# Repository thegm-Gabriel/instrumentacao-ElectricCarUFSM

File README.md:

<div align="center">
  
  <h1>Carro Elétrico UFSM-CS</h1>
  <p><strong>Um laboratório em movimento.</strong></p>
  <p><strong>NEXUS</strong> · sistema de instrumentação, telemetria e controle experimental do veículo</p>
  <p>Universidade Federal de Santa Maria · Campus Cachoeira do Sul</p>
  <p>
    <a href="#o-projeto">O projeto</a> ·
    <a href="#o-sistema">O sistema</a> ·
    <a href="#por-onde-começar">Por onde começar</a> ·
    <a href="documentacao/README.md">Documentação completa</a>
  </p>
</div>

---

## O projeto

O carro reúne, em um veículo experimental, conhecimentos de circuitos,
acionamentos, programação, energia, medição e mecânica. Construí-lo e testá-lo
permite que estudantes confrontem hipóteses com dados reais e entendam como as
decisões de uma área afetam as demais.

O **NEXUS** reúne a instrumentação, a telemetria e o controle experimental do
carro. O nome vem do latim *nexus* (“ligação” ou “vínculo”) e expressa seu
papel de integrar sensores, módulos e informações em uma visão acessível do
veículo. A equipe observa leituras e falhas durante os testes; visitantes
podem conhecer o movimento do carro por um painel de leitura simples. O
projeto também busca aproximar a universidade da comunidade e despertar
interesse pela engenharia e pela mobilidade elétrica.

## O sistema

No NEXUS, três ESP32-S3 dividem aquisição, operação e apresentação dos dados:

```mermaid
flowchart LR
    S["Sensores e encoders"] --> M["ESP32-S3 Mestre"]
    M <-->|UART| E["ESP32-S3 Equipe"]
    M <-->|UART| V["ESP32-S3 Visitantes"]
    M <-->|SPI2| SD["microSD · histórico e logs"]
    E <-->|Wi-Fi / HTTP| PE["Navegador · painel técnico"]
    V <-->|Wi-Fi / HTTP| PV["Navegador · painel público"]
```

| Componente | O que faz |
|---|---|
| **Mestre** | Lê sensores e encoders, calcula a telemetria, registra dados e diagnóstico no microSD e coordena comandos e atualizações OTA. |
| **Equipe** | Recebe a telemetria por UART, hospeda o painel técnico e encaminha consultas e ações ao mestre. |
| **Visitantes** | Recebe a telemetria por UART e apresenta uma página pública de leitura. |
| **Código compartilhado** | Define os formatos dos dados, o enlace UART e os serviços comuns aos firmwares. |

Os firmwares são projetos independentes **PlatformIO/ESP-IDF** em
[`firmware/`](firmware/). A equipe dispõe de páginas separadas para telemetria,
comandos, controle preparatório e diagnóstico dos ESPs. O painel público mostra
as leituras do veículo sem controles de operação.

> **Estado atual do controle:** pedidos de marcha, limites e parada remota são
> registrados no mestre, mas **não acionam fisicamente o veículo**. Ações pelo
> painel da equipe ficam disponíveis aos clientes do AP da Equipe. Veja
> [controle remoto](documentacao/controle-remoto.md) e
> [acesso aos satélites](documentacao/satelites.md).

## Por onde começar

- **Conhecer o funcionamento:** [visão geral da documentação](documentacao/README.md),
  [arquitetura](documentacao/arquitetura.md) e
  [filosofia do código](documentacao/filosofia.md). Para siglas e recursos do
  ESP32-S3, consulte o [glossário e guia de periféricos](documentacao/conceitos.md).
- **Montar e testar:** [pinagem e níveis elétricos](documentacao/pinagem.md),
  [guia do mestre](documentacao/mestre.md) e
  [guia dos satélites](documentacao/satelites.md).
- **Desenvolver e publicar:** [ferramentas](documentacao/ferramentas.md),
  [versionamento, releases e atualização OTA](documentacao/ota.md).

## Equipe

**Orientação:** Prof. Dr. Paulo César Vargas Luz.

**Equipe discente desta etapa de instrumentação:**

- Adylson Hahn
- Érick Ramon Biscaglia
- Gabriel Muttoni
- Gustavo Reckziegel Machado
- Théos Schultz Tompsen

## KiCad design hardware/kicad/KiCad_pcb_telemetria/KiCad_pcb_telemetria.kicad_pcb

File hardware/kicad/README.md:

# Projetos KiCad

Pasta reservada para esquemas elétricos, placas e bibliotecas locais do KiCad.

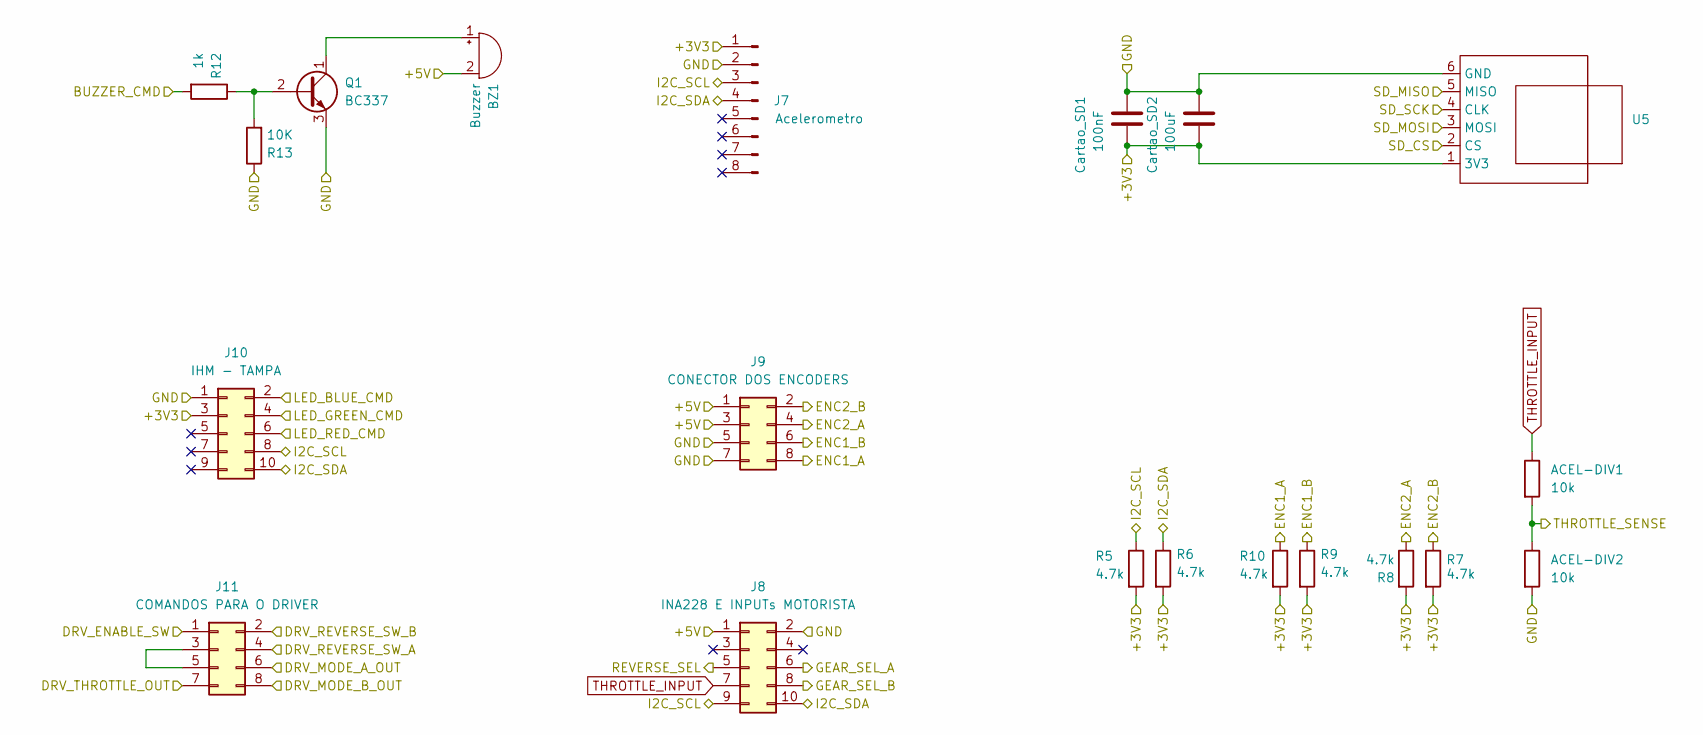
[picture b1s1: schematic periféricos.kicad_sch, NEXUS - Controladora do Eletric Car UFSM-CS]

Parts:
ACEL-DIV1, ACEL-DIV2: 10k; R_Axial_DIN0204_L3.6mm_D1.6mm_P5.08mm_Horizontal
BZ1: Buzzer; Buzzer_D14mm_H7mm_P10mm
Cartao_SD1: 100nF; C_Radial_D5.0mm_H11.0mm_P2.00mm
Cartao_SD2: 100uF; C_Radial_D5.0mm_H11.0mm_P2.00mm
J7: Acelerometro; PinHeader_1x08_P2.54mm_Vertical
J8: INA228 E INPUTs MOTORISTA; JST_PUD_B10B-PUDSS_2x05_P2.00mm_Vertical
J9: CONECTOR DOS ENCODERS; JST_PUD_B08B-PUDSS_2x04_P2.00mm_Vertical
J10: IHM - TAMPA; JST_PUD_B10B-PUDSS_2x05_P2.00mm_Vertical
J11: COMANDOS PARA O DRIVER; JST_PUD_B08B-PUDSS_2x04_P2.00mm_Vertical
Q1: BC337; TO-92
R5, R6, R7, R8, R9, R10: 4.7k; R_Axial_DIN0204_L3.6mm_D1.6mm_P5.08mm_Horizontal
R12: 1k; R_Axial_DIN0204_L3.6mm_D1.6mm_P5.08mm_Horizontal
R13: 10K; R_Axial_DIN0204_L3.6mm_D1.6mm_P5.08mm_Horizontal
U5: CartãoSD-MODULO

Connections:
+3V3: Cartao_SD1.2, Cartao_SD2.2, J7.1, J10.3, R5.2, R6.2, R7.2, R8.2, R9.2, R10.2, U5.1 (3V3); also elsewhere on the board
+5V: BZ1.2 (-), J8.1, J9.1, J9.3; also elsewhere on the board
/CONTROLE DO DRIVER/DRV_ENABLE_SW: J11.1; also elsewhere on the board
/CONTROLE DO DRIVER/DRV_MODE_A_OUT: J11.6; also elsewhere on the board
/CONTROLE DO DRIVER/DRV_MODE_B_OUT: J11.8; also elsewhere on the board
/CONTROLE DO DRIVER/DRV_REVERSE_SW_A: J11.4; also elsewhere on the board
/CONTROLE DO DRIVER/DRV_REVERSE_SW_B: J11.2; also elsewhere on the board
/CONTROLE DO DRIVER/DRV_THROTTLE_OUT: J11.7; also elsewhere on the board
/ESP32-S3-MESTRE/BUZZER_CMD: R12.2; also elsewhere on the board
/ESP32-S3-MESTRE/ENC1_A: J9.8, R10.1; also elsewhere on the board
/ESP32-S3-MESTRE/ENC1_B: J9.6, R9.1; also elsewhere on the board
/ESP32-S3-MESTRE/ENC2_A: J9.4, R8.1; also elsewhere on the board
/ESP32-S3-MESTRE/ENC2_B: J9.2, R7.1; also elsewhere on the board
/ESP32-S3-MESTRE/GEAR_SEL_A: J8.6; also elsewhere on the board
/ESP32-S3-MESTRE/GEAR_SEL_B: J8.8; also elsewhere on the board
/ESP32-S3-MESTRE/LED_BLUE_CMD: J10.2; also elsewhere on the board
/ESP32-S3-MESTRE/LED_GREEN_CMD: J10.4; also elsewhere on the board
/ESP32-S3-MESTRE/LED_RED_CMD: J10.6; also elsewhere on the board
/ESP32-S3-MESTRE/REVERSE_SEL: J8.5; also elsewhere on the board
/ESP32-S3-MESTRE/SD_CS: U5.2 (CS); also elsewhere on the board
/ESP32-S3-MESTRE/SD_MISO: U5.5 (MISO); also elsewhere on the board
/ESP32-S3-MESTRE/SD_MOSI: U5.3 (MOSI); also elsewhere on the board
/ESP32-S3-MESTRE/SD_SCK: U5.4 (CLK); also elsewhere on the board
/ESP32-S3-MESTRE/THROTTLE_SENSE: ACEL-DIV1.2, ACEL-DIV2.1; also elsewhere on the board
GND: ACEL-DIV2.2, Cartao_SD1.1, Cartao_SD2.1, J7.2, J8.2, J9.5, J9.7, J10.1, Q1.3 (E), R13.1, U5.6 (GND); also elsewhere on the board
I2C_SCL: J7.3, J8.9, J10.8, R5.1; also elsewhere on the board
I2C_SDA: J7.4, J8.10, J10.10, R6.1; also elsewhere on the board
unnamed: BZ1.1 (+), Q1.1 (C)
unnamed: J11.3, J11.5
unnamed: Q1.2 (B), R12.1, R13.2
THROTTLE_INPUT: ACEL-DIV1.1, J8.7

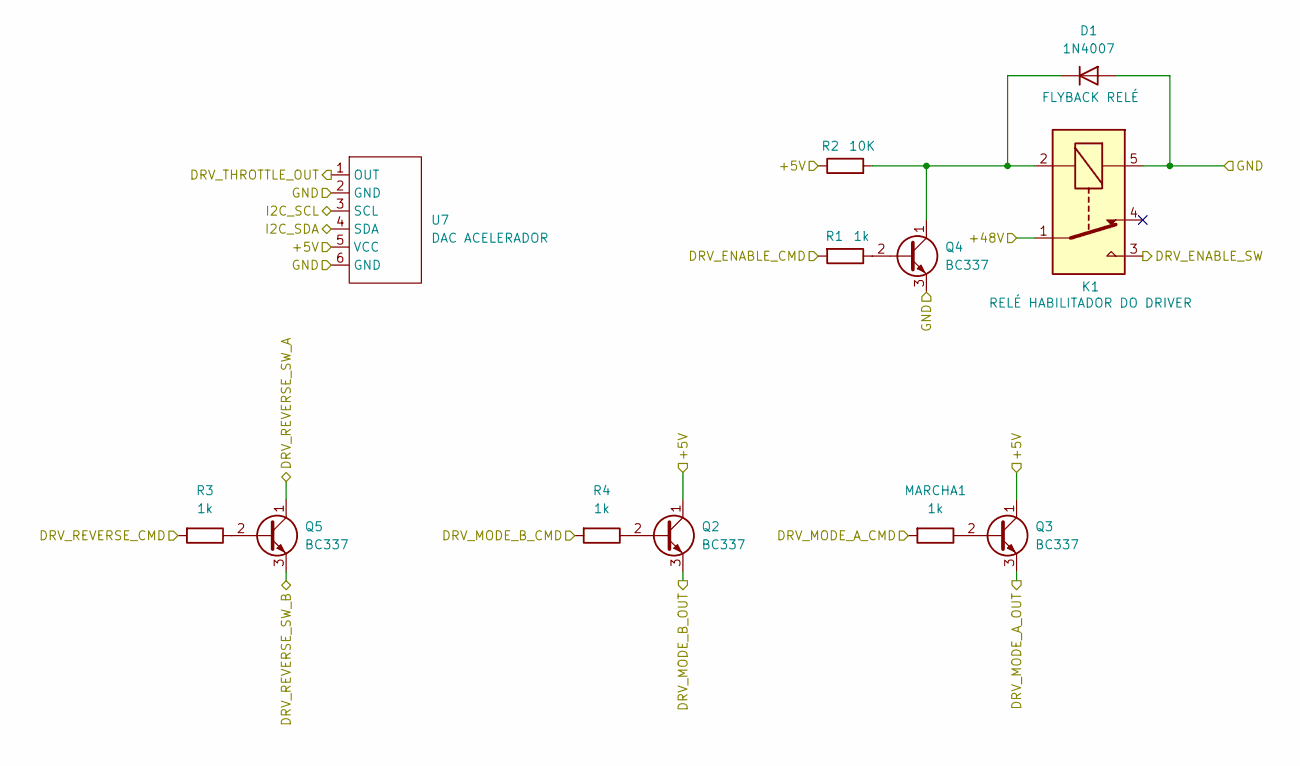
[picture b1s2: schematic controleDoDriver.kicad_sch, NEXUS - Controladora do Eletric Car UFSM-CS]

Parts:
D1: 1N4007; D_DO-41_SOD81_P10.16mm_Horizontal
K1: SANYOU_SRD_Form_C; Relay_SPDT_SANYOU_SRD_Series_Form_C
MARCHA1: 1k; R_Axial_DIN0204_L3.6mm_D1.6mm_P5.08mm_Horizontal
Q2, Q3, Q4, Q5: BC337; TO-92
R1, R3, R4: 1k; R_Axial_DIN0204_L3.6mm_D1.6mm_P5.08mm_Horizontal
R2: 10K; R_Axial_DIN0204_L3.6mm_D1.6mm_P5.08mm_Horizontal
U7: MCP4725

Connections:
+5V: Q2.1 (C), Q3.1 (C), R2.1, U7.5 (VCC); also elsewhere on the board
+48V: K1.1; also elsewhere on the board
/CONTROLE DO DRIVER/DRV_ENABLE_CMD: R1.2; also elsewhere on the board
/CONTROLE DO DRIVER/DRV_ENABLE_SW: K1.3; also elsewhere on the board
/CONTROLE DO DRIVER/DRV_MODE_A_CMD: MARCHA1.2; also elsewhere on the board
/CONTROLE DO DRIVER/DRV_MODE_A_OUT: Q3.3 (E); also elsewhere on the board
/CONTROLE DO DRIVER/DRV_MODE_B_CMD: R4.2; also elsewhere on the board
/CONTROLE DO DRIVER/DRV_MODE_B_OUT: Q2.3 (E); also elsewhere on the board
/CONTROLE DO DRIVER/DRV_REVERSE_CMD: R3.2; also elsewhere on the board
/CONTROLE DO DRIVER/DRV_REVERSE_SW_A: Q5.1 (C); also elsewhere on the board
/CONTROLE DO DRIVER/DRV_REVERSE_SW_B: Q5.3 (E); also elsewhere on the board
/CONTROLE DO DRIVER/DRV_THROTTLE_OUT: U7.1 (OUT); also elsewhere on the board
GND: D1.2 (A), K1.5, Q4.3 (E), U7.2 (GND), U7.6 (GND); also elsewhere on the board
I2C_SCL: U7.3 (SCL); also elsewhere on the board
I2C_SDA: U7.4 (SDA); also elsewhere on the board
unnamed: D1.1 (K), K1.2, Q4.1 (C), R2.2
unnamed: Q2.2 (B), R4.1
unnamed: MARCHA1.1, Q3.2 (B)
unnamed: Q4.2 (B), R1.1
unnamed: Q5.2 (B), R3.1

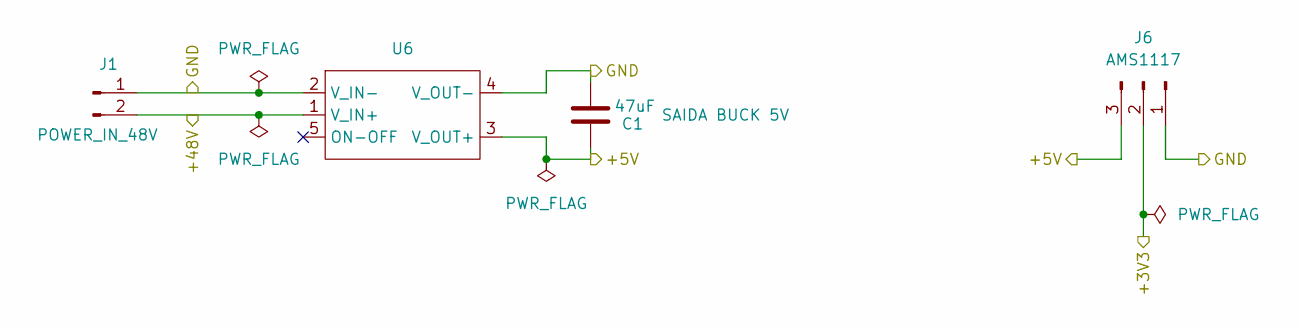
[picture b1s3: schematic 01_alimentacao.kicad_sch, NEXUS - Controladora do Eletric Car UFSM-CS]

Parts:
C1: 47uF; C_Radial_D5.0mm_H11.0mm_P2.00mm
J1: POWER_IN_48V; SolderWire-0.75sqmm_1x02_P4.8mm_D1.25mm_OD2.3mm
J6: AMS1117; PinHeader_1x03_P2.54mm_Vertical
U6: ConversorBUCK_100V_5V-2A

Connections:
+3V3: J6.2; also elsewhere on the board
+5V: C1.1, J6.3, U6.3 (V_OUT+); also elsewhere on the board
+48V: J1.2, U6.1 (V_IN+); also elsewhere on the board
GND: C1.2, J1.1, J6.1, U6.2 (V_IN-), U6.4 (V_OUT-); also elsewhere on the board

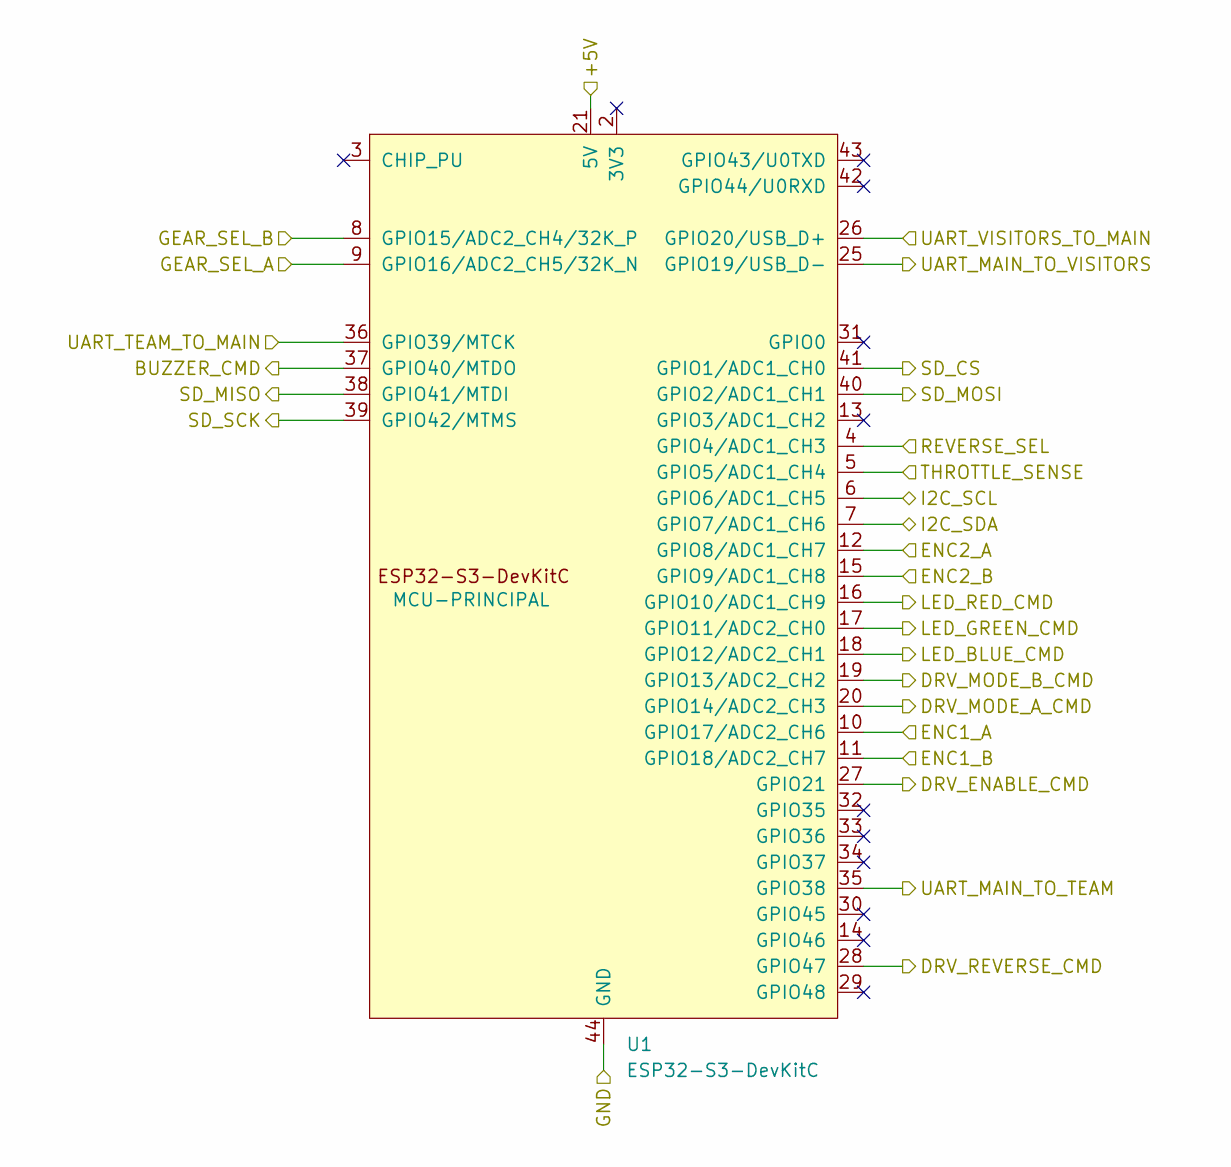
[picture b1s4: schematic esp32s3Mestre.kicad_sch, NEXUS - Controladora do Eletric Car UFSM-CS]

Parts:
U1: ESP32-S3-DevKitC

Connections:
+5V: U1.21 (5V); also elsewhere on the board
/COMUNICAÇÃO WI-FI/UART_MAIN_TO_TEAM: U1.36 (GPIO39/MTCK); also elsewhere on the board
/COMUNICAÇÃO WI-FI/UART_MAIN_TO_VISITORS: U1.25 (GPIO19/USB_D-); also elsewhere on the board
/COMUNICAÇÃO WI-FI/UART_TEAM_TO_MAIN: U1.35 (GPIO38); also elsewhere on the board
/COMUNICAÇÃO WI-FI/UART_VISITORS_TO_MAIN: U1.26 (GPIO20/USB_D+); also elsewhere on the board
/CONTROLE DO DRIVER/DRV_ENABLE_CMD: U1.27 (GPIO21); also elsewhere on the board
/CONTROLE DO DRIVER/DRV_MODE_A_CMD: U1.20 (GPIO14/ADC2_CH3); also elsewhere on the board
/CONTROLE DO DRIVER/DRV_MODE_B_CMD: U1.19 (GPIO13/ADC2_CH2); also elsewhere on the board
/CONTROLE DO DRIVER/DRV_REVERSE_CMD: U1.28 (GPIO47); also elsewhere on the board
/ESP32-S3-MESTRE/BUZZER_CMD: U1.37 (GPIO40/MTDO); also elsewhere on the board
/ESP32-S3-MESTRE/ENC1_A: U1.10 (GPIO17/ADC2_CH6); also elsewhere on the board
/ESP32-S3-MESTRE/ENC1_B: U1.11 (GPIO18/ADC2_CH7); also elsewhere on the board
/ESP32-S3-MESTRE/ENC2_A: U1.12 (GPIO8/ADC1_CH7); also elsewhere on the board
/ESP32-S3-MESTRE/ENC2_B: U1.15 (GPIO9/ADC1_CH8); also elsewhere on the board
/ESP32-S3-MESTRE/GEAR_SEL_A: U1.9 (GPIO16/ADC2_CH5/32K_N); also elsewhere on the board
/ESP32-S3-MESTRE/GEAR_SEL_B: U1.8 (GPIO15/ADC2_CH4/32K_P); also elsewhere on the board
/ESP32-S3-MESTRE/LED_BLUE_CMD: U1.18 (GPIO12/ADC2_CH1); also elsewhere on the board
/ESP32-S3-MESTRE/LED_GREEN_CMD: U1.17 (GPIO11/ADC2_CH0); also elsewhere on the board
/ESP32-S3-MESTRE/LED_RED_CMD: U1.16 (GPIO10/ADC1_CH9); also elsewhere on the board
/ESP32-S3-MESTRE/REVERSE_SEL: U1.4 (GPIO4/ADC1_CH3); also elsewhere on the board
/ESP32-S3-MESTRE/SD_CS: U1.41 (GPIO1/ADC1_CH0); also elsewhere on the board
/ESP32-S3-MESTRE/SD_MISO: U1.38 (GPIO41/MTDI); also elsewhere on the board
/ESP32-S3-MESTRE/SD_MOSI: U1.40 (GPIO2/ADC1_CH1); also elsewhere on the board
/ESP32-S3-MESTRE/SD_SCK: U1.39 (GPIO42/MTMS); also elsewhere on the board
/ESP32-S3-MESTRE/THROTTLE_SENSE: U1.5 (GPIO5/ADC1_CH4); also elsewhere on the board
GND: U1.22 (GND), U1.23 (GND), U1.24 (GND), U1.44 (GND); also elsewhere on the board
I2C_SCL: U1.6 (GPIO6/ADC1_CH5); also elsewhere on the board
I2C_SDA: U1.7 (GPIO7/ADC1_CH6); also elsewhere on the board

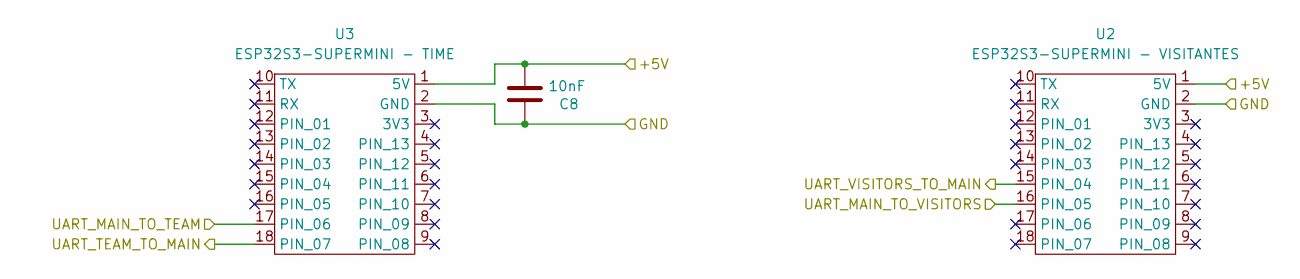
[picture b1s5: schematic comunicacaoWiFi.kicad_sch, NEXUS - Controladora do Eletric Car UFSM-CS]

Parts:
C8: 10nF; C_Radial_D5.0mm_H11.0mm_P2.00mm
U2: ESP32S3-SUPERMINI - VISITANTES; ESP32-S3-SuperMini
U3: ESP32S3-SUPERMINI - TIME; ESP32-S3-SuperMini

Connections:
+5V: C8.2, U2.1 (5V), U3.1 (5V); also elsewhere on the board
/COMUNICAÇÃO WI-FI/UART_MAIN_TO_TEAM: U3.17 (PIN_06); also elsewhere on the board
/COMUNICAÇÃO WI-FI/UART_MAIN_TO_VISITORS: U2.16 (PIN_05); also elsewhere on the board
/COMUNICAÇÃO WI-FI/UART_TEAM_TO_MAIN: U3.18 (PIN_07); also elsewhere on the board
/COMUNICAÇÃO WI-FI/UART_VISITORS_TO_MAIN: U2.15 (PIN_04); also elsewhere on the board
GND: C8.1, U2.2 (GND), U3.2 (GND); also elsewhere on the board

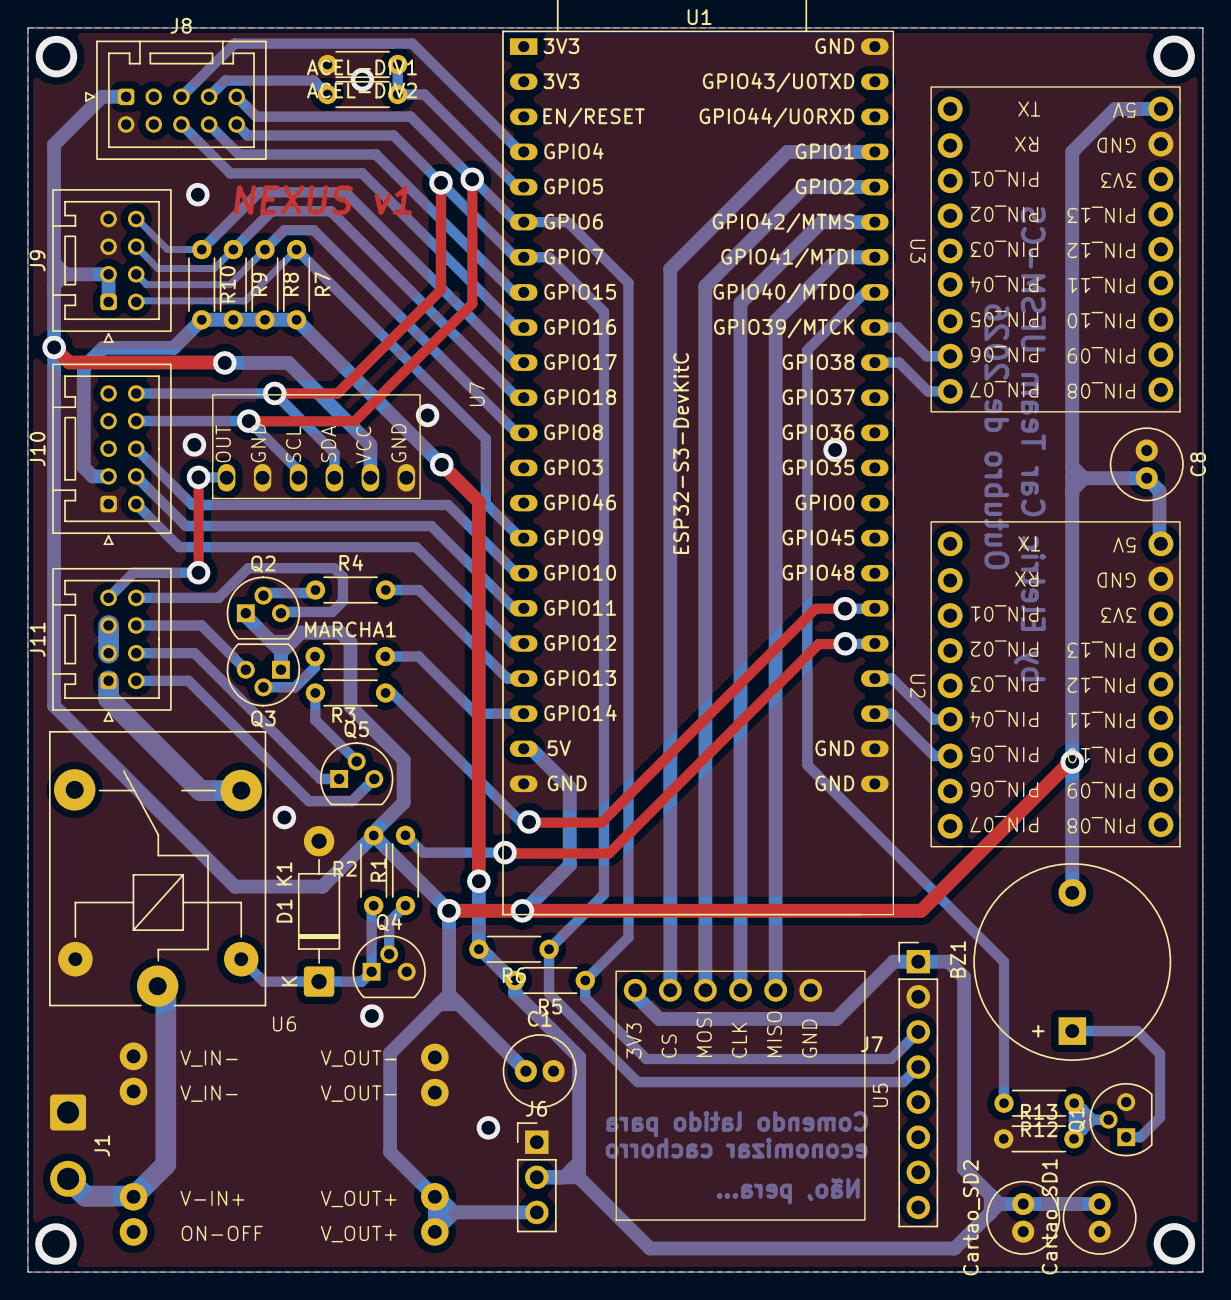
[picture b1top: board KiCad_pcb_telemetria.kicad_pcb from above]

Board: 2 copper layers, 85.0 x 90.0 mm, 40 parts (0 on the bottom side), 45 nets.

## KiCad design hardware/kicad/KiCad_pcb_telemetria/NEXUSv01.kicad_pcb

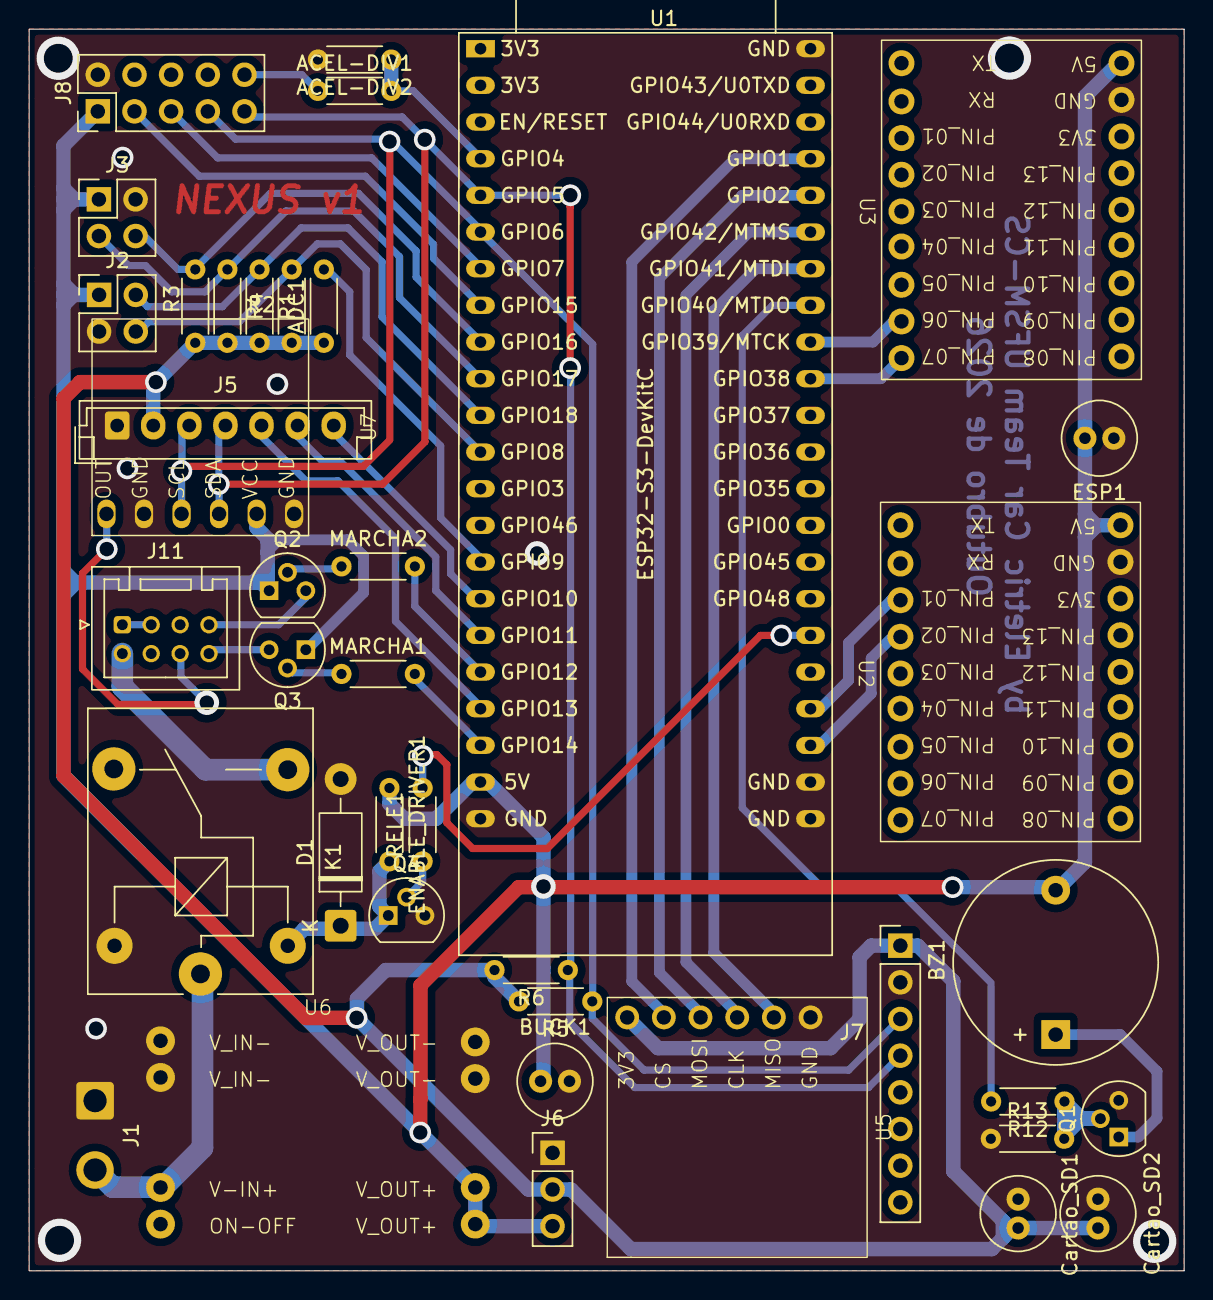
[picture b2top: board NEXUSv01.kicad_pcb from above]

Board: 2 copper layers, 80.0 x 86.0 mm, 40 parts (0 on the bottom side), 41 nets.

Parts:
ACEL-DIV1, ACEL-DIV2: 10k; R_Axial_DIN0204_L3.6mm_D1.6mm_P5.08mm_Horizontal
ADC1: 10k; R_Axial_DIN0204_L3.6mm_D1.6mm_P5.08mm_Horizontal
BUCK1: 47uF; C_Radial_D5.0mm_H11.0mm_P2.00mm
BZ1: Buzzer; Buzzer_D14mm_H7mm_P10mm
Cartao_SD1: 100nF; C_Radial_D5.0mm_H11.0mm_P2.00mm
Cartao_SD2: 100uF; C_Radial_D5.0mm_H11.0mm_P2.00mm
D1: 1N4007; D_DO-41_SOD81_P10.16mm_Horizontal
ENABLE_DRIVER1: 10K; R_Axial_DIN0204_L3.6mm_D1.6mm_P5.08mm_Horizontal
ESP1: 10nF; C_Radial_D5.0mm_H11.0mm_P2.00mm
J1: ALIMENTACAO_48V; SolderWire-0.75sqmm_1x02_P4.8mm_D1.25mm_OD2.3mm
J2, J3: Conn_02x02_Odd_Even; PinHeader_2x02_P2.54mm_Vertical
J5: INDICADOR; JST_EH_B7B-EH-A_1x07_P2.50mm_Vertical
J6: AMS1117; PinHeader_1x03_P2.54mm_Vertical
J7: Acelerometro; PinHeader_1x08_P2.54mm_Vertical
J8: Conn_02x05_Odd_Even; PinHeader_2x05_P2.54mm_Vertical
J11: Conn_02x04_Odd_Even; JST_PUD_B08B-PUDSS_2x04_P2.00mm_Vertical
K1: SANYOU_SRD_Form_C; Relay_SPDT_SANYOU_SRD_Series_Form_C
MARCHA1, MARCHA2: 1k; R_Axial_DIN0204_L3.6mm_D1.6mm_P5.08mm_Horizontal
Q1, Q2, Q3, Q4: BC337; TO-92
R1, R2, R3, R4, R5, R6: 4.7k; R_Axial_DIN0204_L3.6mm_D1.6mm_P5.08mm_Horizontal
R12: 1k; R_Axial_DIN0204_L3.6mm_D1.6mm_P5.08mm_Horizontal
R13: 10K; R_Axial_DIN0204_L3.6mm_D1.6mm_P5.08mm_Horizontal
RELE1: 1k; R_Axial_DIN0204_L3.6mm_D1.6mm_P5.08mm_Horizontal
U1: ESP32-S3-DevKitC
U2: ESP32S3-SUPERMINI - VISITANTES; ESP32-S3-SuperMini
U3: ESP32S3-SUPERMINI - TIME; ESP32-S3-SuperMini
U5: CartãoSD-MODULO
U6: ConversorBUCK_100V_5V-2A
U7: MCP4725

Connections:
+3V3: ADC1.1, Cartao_SD1.2, Cartao_SD2.2, J5.2, J6.2, J7.1, R1.2, R2.2, R3.2, R4.2, R5.2, R6.2, U5.1 (3V3)
+5V: BUCK1.1, BZ1.2 (-), ENABLE_DRIVER1.1, ESP1.2, J2.1, J3.1, J6.3, J8.1, Q2.1 (C), Q3.1 (C), U1.21 (5V), U2.1 (5V), U3.1 (5V), U6.3 (V_OUT+), U7.5 (VCC)
+48V: J1.2, K1.1, U6.1 (V_IN+)
AFERIR_TENSAO_3V3: ADC1.2, U1.15 (GPIO9/ADC1_CH8)
ENABLE_DRIVER: J11.2, K1.3
GND: ACEL-DIV2.2, BUCK1.2, Cartao_SD1.1, Cartao_SD2.1, D1.2 (A), ESP1.1, J1.1, J2.3, J3.2, J5.1, J6.1, J7.2, J8.2, K1.5, Q1.3 (E), Q4.3 (E), R13.1, U1.22 (GND), U1.23 (GND), U1.24 (GND), U1.44 (GND), U2.2 (GND), U3.2 (GND), U5.6 (GND), U6.2 (V_IN-), U6.4 (V_OUT-), U7.2 (GND), U7.6 (GND)
MARCHA-A: J8.3, U1.8 (GPIO15/ADC2_CH4/32K_P)
MARCHA-A-OUT: MARCHA1.2, U1.20 (GPIO14/ADC2_CH3)
MARCHA-A-conector: J11.8, Q3.3 (E)
MARCHA-B: J8.5, U1.7 (GPIO7/ADC1_CH6)
MARCHA-B-OUT: MARCHA2.2, U1.18 (GPIO12/ADC2_CH1)
MARCHA-B-conector: J11.7, Q2.3 (E)
unnamed: BZ1.1 (+), Q1.1 (C)
unnamed: D1.1 (K), ENABLE_DRIVER1.2, K1.2, Q4.1 (C)
unnamed: J11.1, J11.3
unnamed: Q1.2 (B), R12.1, R13.2
unnamed: MARCHA2.1, Q2.2 (B)
unnamed: MARCHA1.1, Q3.2 (B)
unnamed: Q4.2 (B), RELE1.1
S3MESTRE-ENABLE_DRIVER: RELE1.2, U1.28 (GPIO47)
S3MESTRE-GPIO4-ENCODER01_A: J3.4, R3.1, U1.9 (GPIO16/ADC2_CH5/32K_N)
S3MESTRE-GPIO5-ENCODER01_B: J3.3, R4.1, U1.10 (GPIO17/ADC2_CH6)
S3MESTRE-GPIO6-ENCODER02_A: J2.2, R1.1, U1.11 (GPIO18/ADC2_CH7)
S3MESTRE-GPIO7-ENCODER02_B: J2.4, R2.1, U1.12 (GPIO8/ADC1_CH7)
S3MESTRE-GPIO8-I2C_SDA: J5.4, J7.4, J8.9, R6.1, U1.5 (GPIO5/ADC1_CH4), U7.4 (SDA)
S3MESTRE-GPIO9-I2C_SCL: J5.3, J7.3, J8.7, R5.1, U1.6 (GPIO6/ADC1_CH5), U7.3 (SCL)
S3MESTRE-GPIO10-LED_VERDE: J5.6, U1.17 (GPIO11/ADC2_CH0)
S3MESTRE-GPIO12-LED_VERMELHO: J5.7, U1.16 (GPIO10/ADC1_CH9)
S3MESTRE-GPIO13-LED_AZUL: J5.5, U1.19 (GPIO13/ADC2_CH2)
S3MESTRE-GPIO14-BUZZER: R12.2, U1.37 (GPIO40/MTDO)
S3MESTRE-GPIO15-SD_CS: U1.41 (GPIO1/ADC1_CH0), U5.2 (CS)
S3MESTRE-GPIO16-SD_MOSI: U1.40 (GPIO2/ADC1_CH1), U5.3 (MOSI)
S3MESTRE-GPIO17-SD_SCK: U1.39 (GPIO42/MTMS), U5.4 (CLK)
S3MESTRE-GPIO18-SD_MISO: U1.38 (GPIO41/MTDI), U5.5 (MISO)
S3MESTRE-GPIO39-TX_VISITANTES: U1.25 (GPIO19/USB_D-), U2.13 (PIN_02)
S3MESTRE-GPIO40-RX_VISITANTES: U1.26 (GPIO20/USB_D+), U2.12 (PIN_01)
S3MESTRE-GPIO41-TX_EQUIPE: U1.35 (GPIO38), U3.18 (PIN_07)
S3MESTRE-GPIO42-RX_EQUIPE: U1.36 (GPIO39/MTCK), U3.17 (PIN_06)
SGN_ACEL: ACEL-DIV1.2, ACEL-DIV2.1, U1.4 (GPIO4/ADC1_CH3)
SGN_ACEL_CONECTOR: ACEL-DIV1.1, J8.10
SINAL-DAC-ACELERADOR: J11.6, U7.1 (OUT)

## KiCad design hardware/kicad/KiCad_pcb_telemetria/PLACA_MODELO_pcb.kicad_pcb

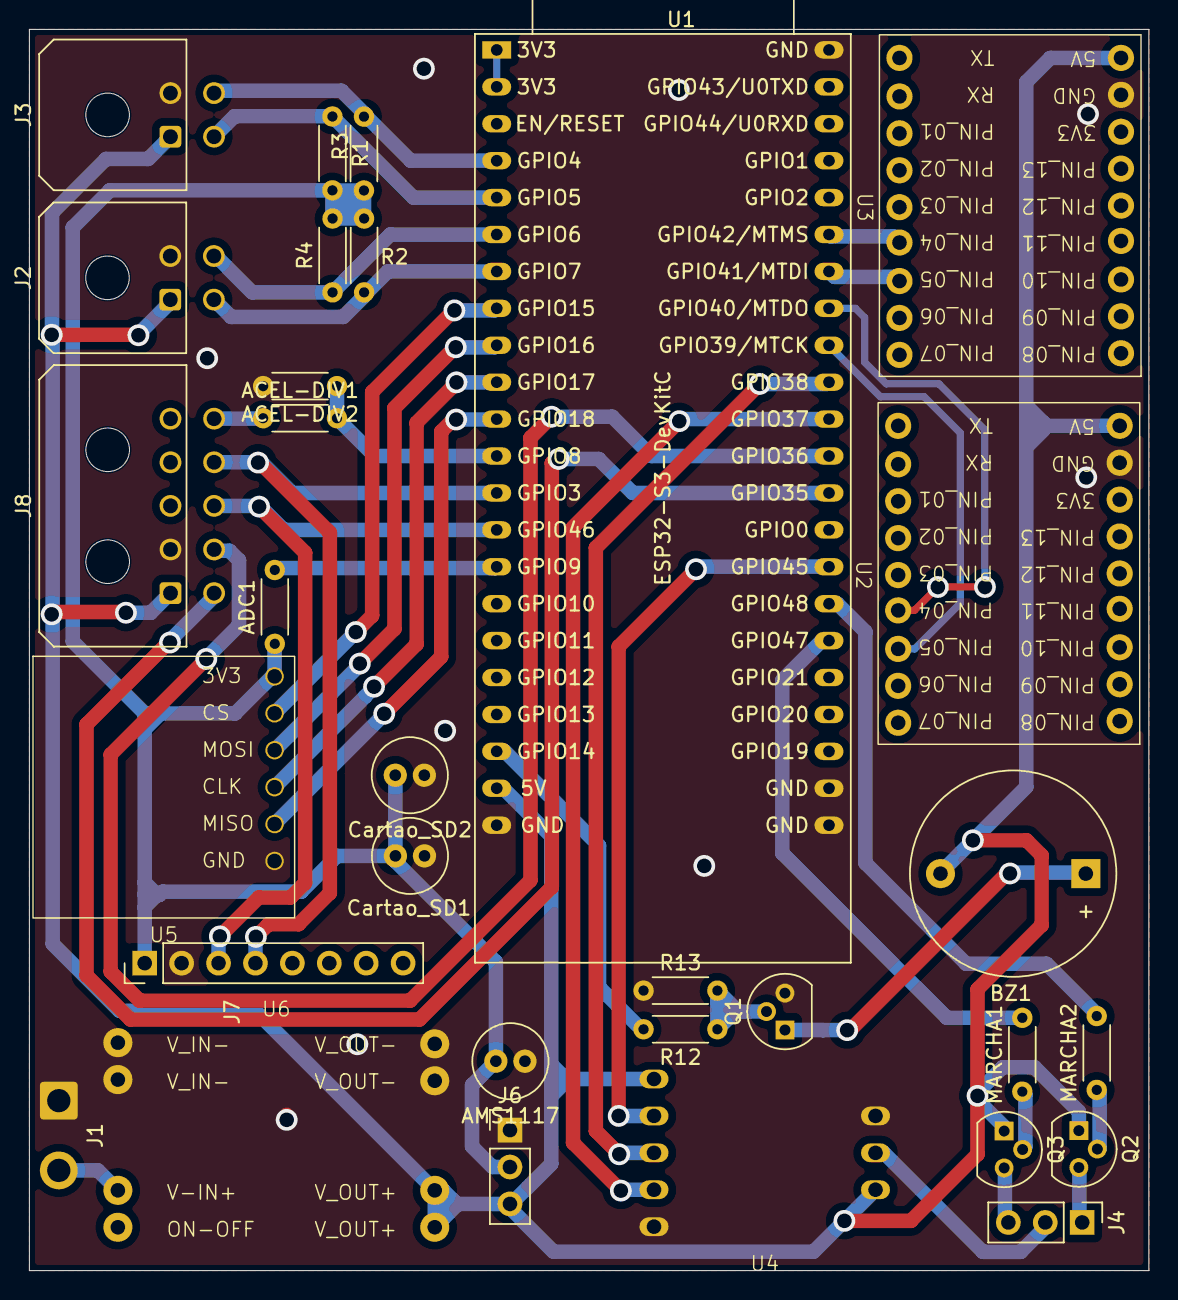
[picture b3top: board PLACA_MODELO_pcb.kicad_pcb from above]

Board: 2 copper layers, 77.0 x 85.4 mm, 31 parts (0 on the bottom side), 37 nets.

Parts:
ACEL-DIV1, ACEL-DIV2: 10k; R_Axial_DIN0204_L3.6mm_D1.6mm_P5.08mm_Horizontal
ADC1: 10k; R_Axial_DIN0204_L3.6mm_D1.6mm_P5.08mm_Horizontal
AMS1117: 10uF; C_Radial_D5.0mm_H11.0mm_P2.00mm
BZ1: Buzzer; Buzzer_D14mm_H7mm_P10mm
Cartao_SD1: 100nF; C_Radial_D5.0mm_H11.0mm_P2.00mm
Cartao_SD2: 100uF; C_Radial_D5.0mm_H11.0mm_P2.00mm
J1: ALIMENTACAO_48V; SolderWire-0.75sqmm_1x02_P4.8mm_D1.25mm_OD2.3mm
J2, J3: Conn_02x02_Odd_Even; Molex_Micro-Fit_3.0_43045-0400_2x02_P3.00mm_Horizontal
J4: Conn_01x03_Pin; PinHeader_1x03_P2.54mm_Vertical
J6: AMS1117; PinHeader_1x03_P2.54mm_Vertical
J7: Acelerometro; PinHeader_1x08_P2.54mm_Vertical
J8: Conn_02x05_Odd_Even; Molex_Micro-Fit_3.0_43045-1000_2x05_P3.00mm_Horizontal
MARCHA1, MARCHA2: 1k; R_Axial_DIN0204_L3.6mm_D1.6mm_P5.08mm_Horizontal
Q1, Q2, Q3: BC337; TO-92
R1, R2, R3, R4: 4.7k; R_Axial_DIN0204_L3.6mm_D1.6mm_P5.08mm_Horizontal
R12: 1k; R_Axial_DIN0204_L3.6mm_D1.6mm_P5.08mm_Horizontal
R13: 10K; R_Axial_DIN0204_L3.6mm_D1.6mm_P5.08mm_Horizontal
U1: ESP32-S3-DevKitC
U2: ESP32S3-SUPERMINI - VISITANTES; ESP32-S3-SuperMini
U3: ESP32S3-SUPERMINI - TIME; ESP32-S3-SuperMini
U4: X9C103S
U5: CartãoSD-MODULO
U6: ConversorBUCK_100V_5V-2A

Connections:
+3V3: ADC1.1, AMS1117.2, Cartao_SD1.2, Cartao_SD2.2, J6.2, J7.1, R1.2, R2.2, R3.2, R4.2, U5.1 (3V3)
+5V: BZ1.2 (-), J2.1, J3.1, J6.3, J8.1, Q2.1 (C), Q3.1 (C), U1.21 (5V), U2.1 (5V), U3.1 (5V), U4.5 (VCC), U4.6 (VH), U6.3 (V_OUT+)
CS: U1.30 (GPIO45), U4.4 (CS)
GND: ACEL-DIV2.2, AMS1117.1, Cartao_SD1.1, Cartao_SD2.1, J1.1, J2.2, J3.2, J6.1, J7.2, J8.2, Q1.3 (E), R13.1, U1.22 (GND), U1.23 (GND), U1.24 (GND), U1.44 (GND), U2.2 (GND), U3.2 (GND), U4.1 (GND), U4.8 (VL), U5.6 (GND), U6.2 (V_IN-), U6.4 (V_OUT-)
INC: U1.35 (GPIO38), U4.3 (INC)
MARCHA-A: J8.6, U1.32 (GPIO35)
MARCHA-A-OUT: MARCHA1.2, U1.28 (GPIO47)
MARCHA-A-conector: J4.3, Q3.3 (E)
MARCHA-B: J8.7, U1.33 (GPIO36)
MARCHA-B-OUT: MARCHA2.2, U1.29 (GPIO48)
MARCHA-B-conector: J4.1, Q2.3 (E)
unnamed: BZ1.1 (+), Q1.1 (C)
unnamed: J1.2, U6.1 (V_IN+)
unnamed: J4.2, U4.7 (W)
unnamed: Q1.2 (B), R12.1, R13.2
unnamed: MARCHA2.1, Q2.2 (B)
unnamed: MARCHA1.1, Q3.2 (B)
unnamed: U1.1 (3V3), U1.2 (3V3)
S3MESTRE-GPIO4-ENCODER01_A: J3.4, R3.1, U1.4 (GPIO4/ADC1_CH3)
S3MESTRE-GPIO5-ENCODER01_B: J2.4, R4.1, U1.6 (GPIO6/ADC1_CH5)
S3MESTRE-GPIO6-ENCODER02_A: J3.3, R1.1, U1.5 (GPIO5/ADC1_CH4)
S3MESTRE-GPIO7-ENCODER02_B: J2.3, R2.1, U1.7 (GPIO7/ADC1_CH6)
S3MESTRE-GPIO8-I2C_SDA: J7.4, J8.9, U1.13 (GPIO3/ADC1_CH2)
S3MESTRE-GPIO9: ADC1.2, U1.15 (GPIO9/ADC1_CH8)
S3MESTRE-GPIO9-I2C_SCL: J7.3, J8.8, U1.14 (GPIO46)
S3MESTRE-GPIO14-BUZZER: R12.2, U1.20 (GPIO14/ADC2_CH3)
S3MESTRE-GPIO15-SD_CS: U1.8 (GPIO15/ADC2_CH4/32K_P), U5.2 (CS)
S3MESTRE-GPIO16-SD_MOSI: U1.9 (GPIO16/ADC2_CH5/32K_N), U5.3 (MOSI)
S3MESTRE-GPIO17-SD_SCK: U1.10 (GPIO17/ADC2_CH6), U5.4 (CLK)
S3MESTRE-GPIO18-SD_MISO: U1.11 (GPIO18/ADC2_CH7), U5.5 (MISO)
S3MESTRE-GPIO39-TX_VISITANTES: U1.36 (GPIO39/MTCK), U2.16 (PIN_05)
S3MESTRE-GPIO40-RX_VISITANTES: U1.37 (GPIO40/MTDO), U2.15 (PIN_04)
S3MESTRE-GPIO41-TX_EQUIPE: U1.38 (GPIO41/MTDI), U3.16 (PIN_05)
S3MESTRE-GPIO42-RX_EQUIPE: U1.39 (GPIO42/MTMS), U3.15 (PIN_04)
SGN_ACEL: ACEL-DIV1.2, ACEL-DIV2.1, U1.12 (GPIO8/ADC1_CH7)
SGN_ACEL_CONECTOR: ACEL-DIV1.1, J8.10
U/D: U1.34 (GPIO37), U4.2 (U/D)
